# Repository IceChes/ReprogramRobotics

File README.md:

# ReprogramRobotics
This repository contains the raw firmware for my combat robots, as well as CAD and information about the ones that I've designed.

# Firmware Folder
Contains as-is firmware files. You should be able to work with Arduino directly in here. There are also compiled firmware files in here. If you want documentation for non-prototype firmware, that's also in here. All firmware, unless noted otherwise, is GPL3 licensed.

# Hardware Folder
Non-robot pieces of hardware, including Kicad workspaces, pieces of universal hardware (of which this ecosystem has few), and transmitter versions. All hardware, unless noted otherwise, is under the OHL-W license.

# Robot CAD Folder
Robot CAD and fab files, occasionally including build instructions and BOMs. All robots are of original design and licensed under OHL-W.

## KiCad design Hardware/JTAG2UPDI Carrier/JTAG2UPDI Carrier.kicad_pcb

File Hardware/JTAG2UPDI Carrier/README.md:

jtag2updi is no longer recommended as a protocol for programming UPDI chips. I just find it to be very easy to use.

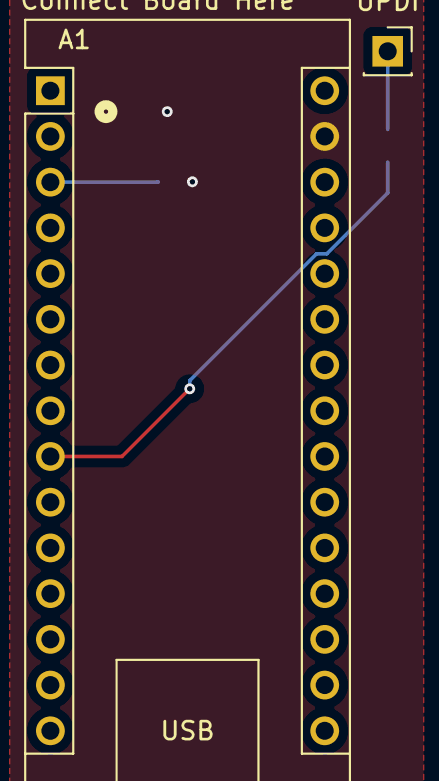
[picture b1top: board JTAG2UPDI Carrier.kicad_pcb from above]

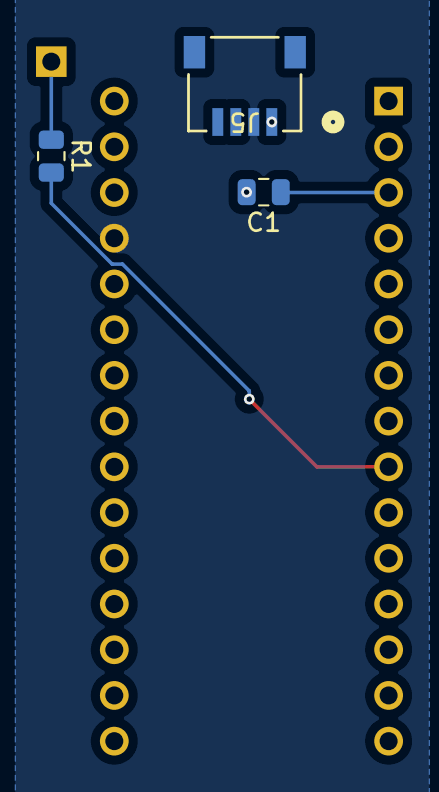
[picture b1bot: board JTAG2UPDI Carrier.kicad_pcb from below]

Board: 2 copper layers, 5 parts (3 on the bottom side), 5 nets.

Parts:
A1: Arduino_Nano_v3.x; Arduino_Nano
C1: C; C_0805_2012Metric
J5: PRT-14417; CONN_PRT-14417_SPK
R1: R; R_0805_2012Metric
UPDI: Conn_01x01_Socket; PinSocket_1x01_P2.54mm_Vertical

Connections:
+5V: A1.27 (+5V), J5.2
GND: A1.29 (GND), C1.2, J5.1
unnamed: A1.9 (D6), R1.2
unnamed: A1.3 (~RESET), C1.1
unnamed: R1.1, UPDI.1

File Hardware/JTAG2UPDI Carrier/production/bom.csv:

Designator,Footprint,Quantity,Value,LCSC Part #
A1,Arduino_Nano,1,Arduino_Nano_v3.x,
C1,0805,1,C,
J5,CONN_PRT-14417_SPK,1,PRT-14417,
R1,0805,1,R,
UPDI,PinSocket_1x01_P2.54mm_Vertical,1,Conn_01x01_Socket,

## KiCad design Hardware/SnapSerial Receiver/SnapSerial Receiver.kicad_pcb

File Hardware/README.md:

# Hardware
3D files and PCBs that aren't robots.

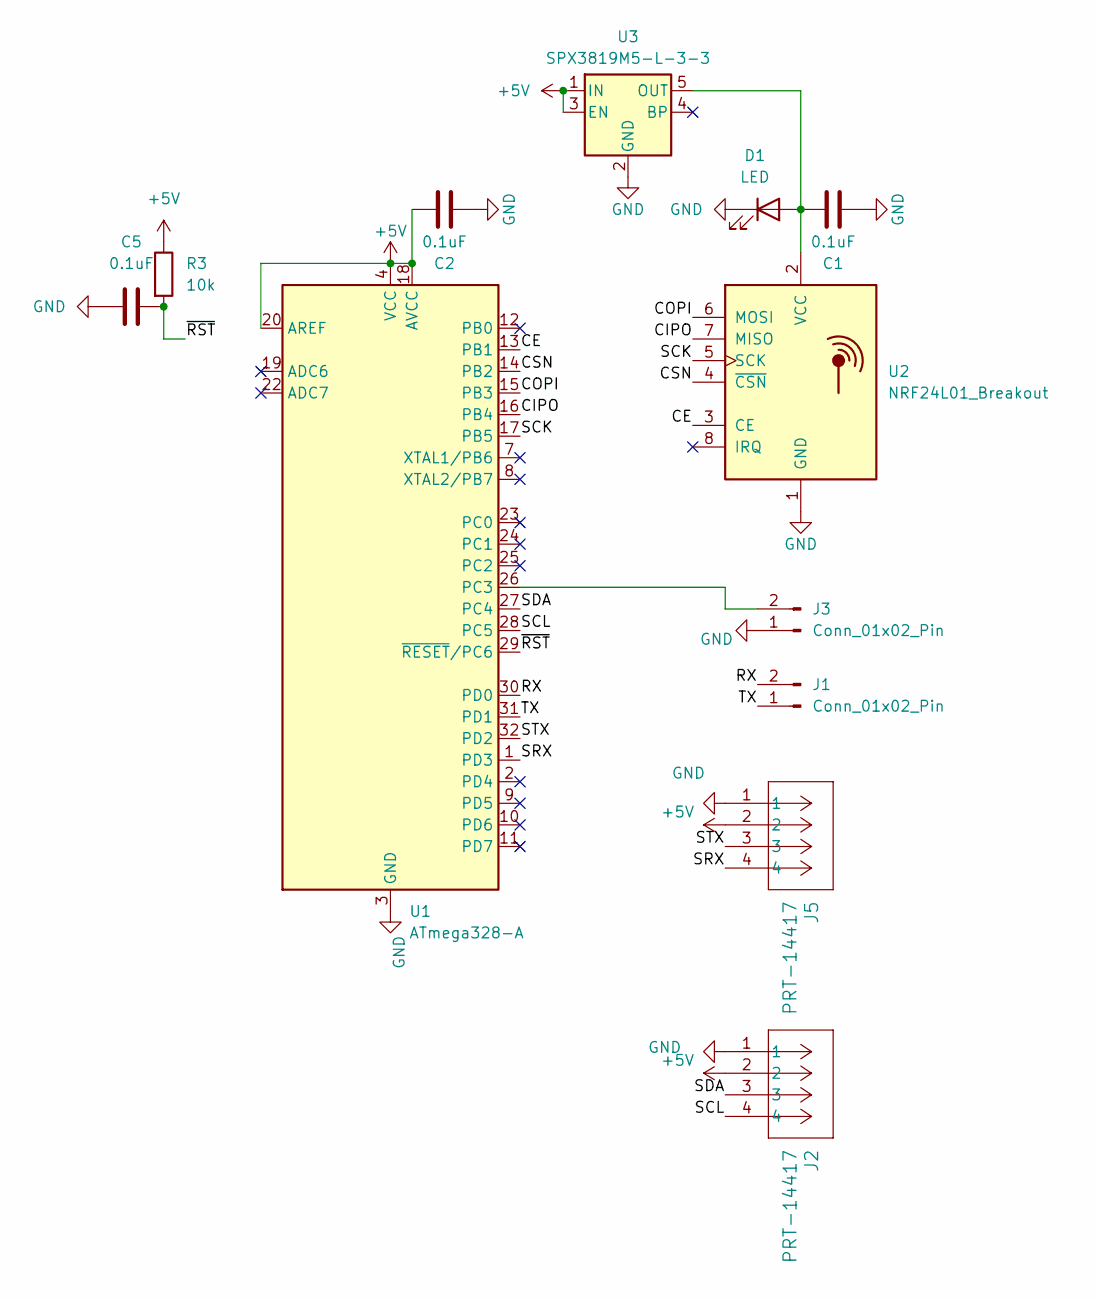
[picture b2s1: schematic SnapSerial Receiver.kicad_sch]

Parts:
C1, C2, C5: 0.1uF; C_0805_2012Metric
D1: LED; LED_0805_2012Metric
J1, J3: Conn_01x02_Pin; PinHeader_1x02_P2.54mm_Vertical
J2, J5: PRT-14417; CONN_PRT-14417_SPK
R3: 10k; R_0805_2012Metric
U1: ATmega328-A; TQFP-32_7x7mm_P0.8mm
U2: NRF24L01_Breakout; nRF24L01_Breakout
U3: SPX3819M5-L-3-3; SOT-23-5

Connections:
+5V: C2.2, J2.2, J5.2, R3.1, U1.4 (VCC), U1.6 (VCC), U1.18 (AVCC), U1.20 (AREF), U3.1 (IN), U3.3 (EN)
/CE: U1.13 (PB1), U2.3 (CE)
/CIPO: U1.16 (PB4), U2.7 (MISO)
/COPI: U1.15 (PB3), U2.6 (MOSI)
/CSN: U1.14 (PB2), U2.4 (~CSN)
/RX: J1.2, U1.30 (PD0)
/SCK: U1.17 (PB5), U2.5 (SCK)
/SCL: J2.4, U1.28 (PC5)
/SDA: J2.3, U1.27 (PC4)
/SRX: J5.4, U1.1 (PD3)
/STX: J5.3, U1.32 (PD2)
/TX: J1.1, U1.31 (PD1)
/~RST: C5.2, R3.2, U1.29 (~RESET/PC6)
GND: C1.1, C2.1, C5.1, D1.1 (K), J2.1, J3.1, J5.1, U1.3 (GND), U1.5 (GND), U1.21 (GND), U2.1 (GND), U3.2 (GND)
unnamed: C1.2, D1.2 (A), U2.2 (VCC), U3.5 (OUT)
unnamed: J3.2, U1.26 (PC3)

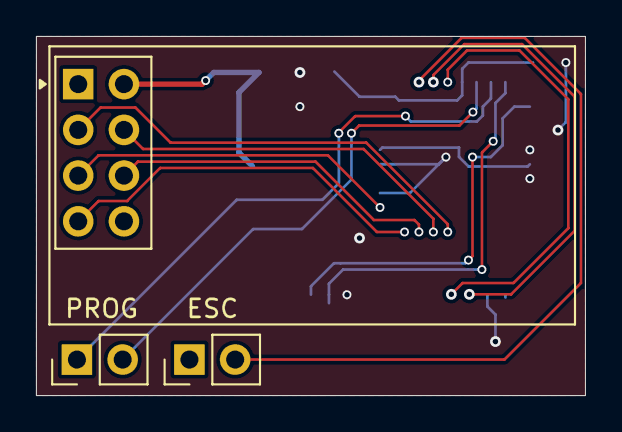
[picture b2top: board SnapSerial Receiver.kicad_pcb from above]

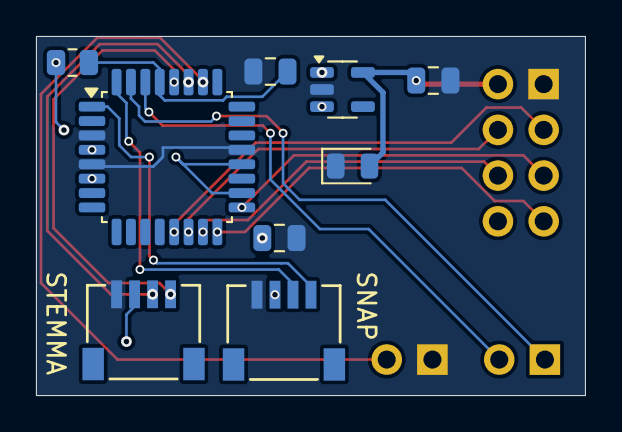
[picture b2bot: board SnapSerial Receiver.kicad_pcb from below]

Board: 2 copper layers, 30.5 x 20.0 mm, 12 parts (9 on the bottom side), 16 nets.

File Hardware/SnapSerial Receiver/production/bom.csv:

Designator,Footprint,Quantity,Value,LCSC Part #
"C1, C2, C5",0805,3,0.1uF,
D1,0805,1,LED,
"J1, J3",PinHeader_1x02_P2.54mm_Vertical,2,Conn_01x02_Pin,
"J2, J5",CONN_PRT-14417_SPK,2,PRT-14417,
R3,0805,1,10k,
U1,TQFP-32_7x7mm_P0.8mm,1,ATmega328-A,
U2,nRF24L01_Breakout,1,NRF24L01_Breakout,
U3,SOT-23-5,1,SPX3819M5-L-3-3,

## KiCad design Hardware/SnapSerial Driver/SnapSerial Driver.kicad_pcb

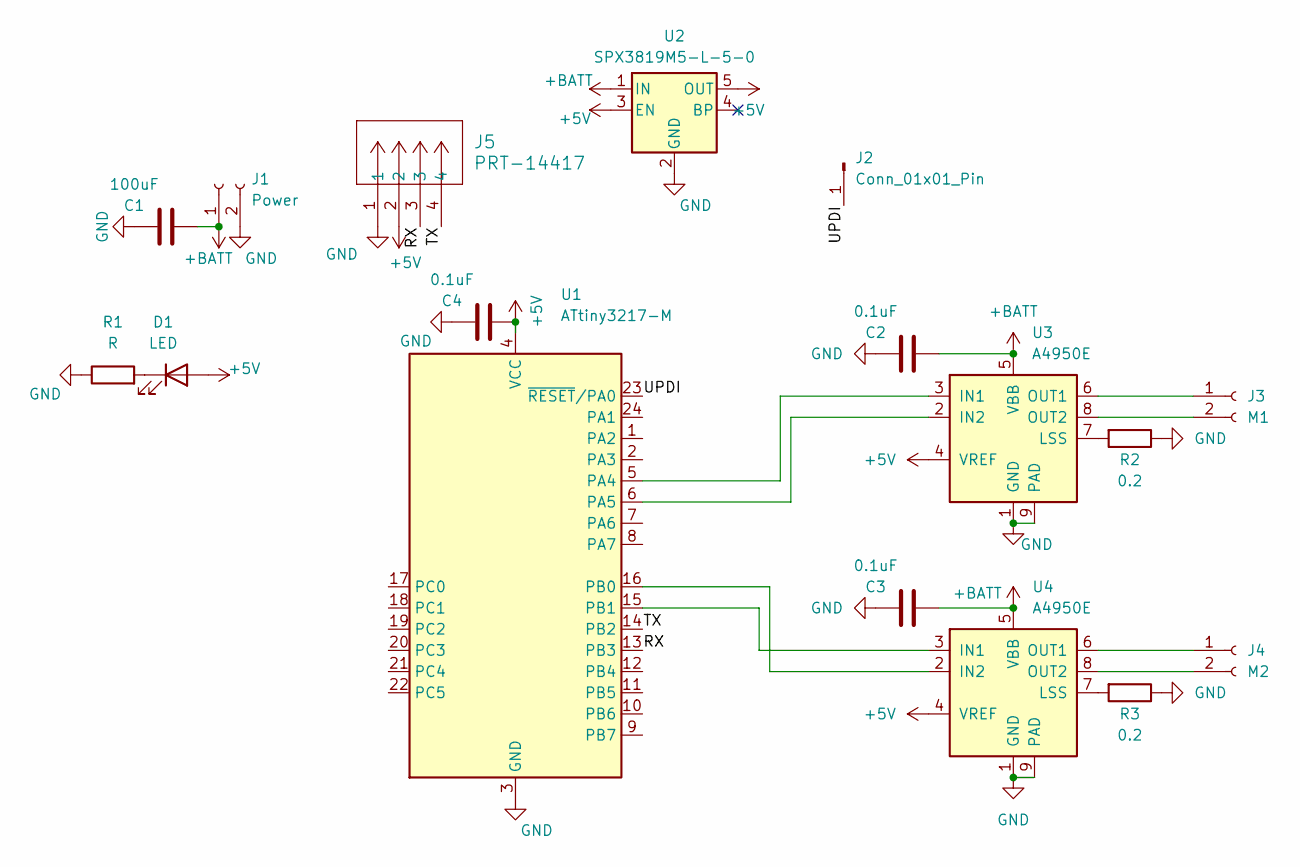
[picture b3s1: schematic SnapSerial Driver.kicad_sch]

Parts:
C1: 100uF; C_1206_3216Metric
C2, C3, C4: 0.1uF; C_0805_2012Metric
D1: LED; LED_0805_2012Metric
J1: Power; PinSocket_1x02_P2.54mm_Vertical
J2: Conn_01x01_Pin; PinHeader_1x01_P2.54mm_Vertical
J3: M1; PinSocket_1x02_P2.54mm_Vertical
J4: M2; PinSocket_1x02_P2.54mm_Vertical
J5: PRT-14417; CONN_PRT-14417_SPK
R1: R; R_0805_2012Metric
R2, R3: 0.2; R_0805_2012Metric
U1: ATtiny3217-M; QFN-24-1EP_4x4mm_P0.5mm_EP2.6x2.6mm
U2: SPX3819M5-L-5-0; SOT-23-5
U3, U4: A4950E; SOIC-8-1EP_3.9x4.9mm_P1.27mm_EP2.41x3.3mm

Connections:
+5V: C4.1, D1.2 (A), J5.2, U1.4 (VCC), U2.3 (EN), U2.5 (OUT), U3.4 (VREF), U4.4 (VREF)
+BATT: C1.1, C2.1, C3.1, J1.1, U2.1 (IN), U3.5 (VBB), U4.5 (VBB)
/RX: J5.3, U1.13 (PB3)
/TX: J5.4, U1.14 (PB2)
/UPDI: J2.1, U1.23 (~RESET/PA0)
GND: C1.2, C2.2, C3.2, C4.2, J1.2, J5.1, R1.1, R2.1, R3.1, U1.3 (GND), U1.25 (GND), U2.2 (GND), U3.1 (GND), U3.9 (PAD), U4.1 (GND), U4.9 (PAD)
unnamed: D1.1 (K), R1.2
unnamed: J3.1, U3.6 (OUT1)
unnamed: J3.2, U3.8 (OUT2)
unnamed: J4.1, U4.6 (OUT1)
unnamed: J4.2, U4.8 (OUT2)
unnamed: U1.5 (PA4), U3.3 (IN1)
unnamed: U1.6 (PA5), U3.2 (IN2)
unnamed: U1.16 (PB0), U4.2 (IN2)
unnamed: U1.15 (PB1), U4.3 (IN1)
unnamed: R2.2, U3.7 (LSS)
unnamed: R3.2, U4.7 (LSS)

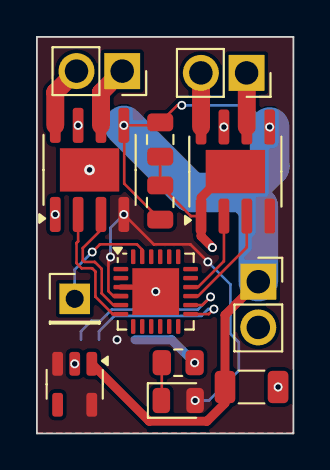
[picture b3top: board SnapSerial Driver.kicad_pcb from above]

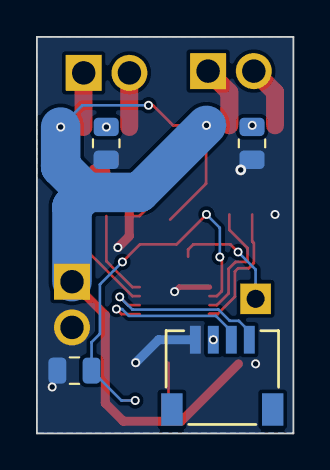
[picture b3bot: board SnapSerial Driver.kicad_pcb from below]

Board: 2 copper layers, 14.2 x 22.0 mm, 17 parts (4 on the bottom side), 17 nets.

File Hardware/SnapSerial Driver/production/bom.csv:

Designator,Footprint,Quantity,Value,LCSC Part #
C1,1206,1,100uF,
"C2, C3, C4",0805,3,0.1uF,
D1,0805,1,LED,
J1,PinSocket_1x02_P2.54mm_Vertical,1,Power,
J2,PinHeader_1x01_P2.54mm_Vertical,1,Conn_01x01_Pin,
J3,PinSocket_1x02_P2.54mm_Vertical,1,M1,
J4,PinSocket_1x02_P2.54mm_Vertical,1,M2,
J5,CONN_PRT-14417_SPK,1,PRT-14417,
R1,0805,1,R,
"R2, R3",0805,2,0.2,
U1,QFN-24-1EP_4x4mm_P0.5mm_EP2.6x2.6mm,1,ATtiny3217-M,
U2,SOT-23-5,1,SPX3819M5-L-5-0,
"U3, U4",SOIC-8-1EP_3.9x4.9mm_P1.27mm_EP2.41x3.3mm,2,A4950E,

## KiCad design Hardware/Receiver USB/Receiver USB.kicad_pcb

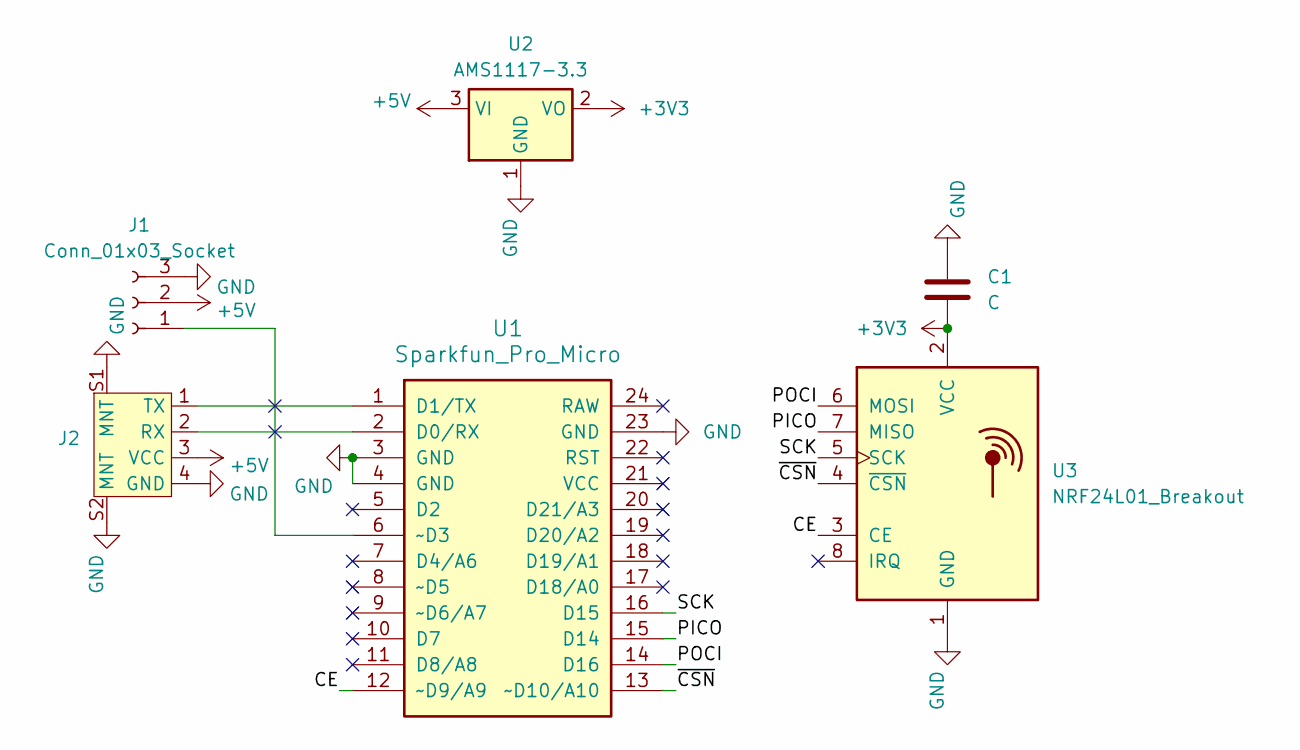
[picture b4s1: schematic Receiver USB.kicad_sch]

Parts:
C1: C; C_0805_2012Metric
J1: Conn_01x03_Socket; PinHeader_1x03_P2.54mm_Vertical
J2: SPARKFUN_PRT-14417
U1: Sparkfun_Pro_Micro
U2: AMS1117-3.3; SOT-223-3_TabPin2
U3: NRF24L01_Breakout; nRF24L01_Breakout

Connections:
+3V3: C1.2, U2.2 (VO), U3.2 (VCC)
+5V: J1.2, J2.3 (VCC), U2.3 (VI)
/CE: U1.12 (~D9/A9), U3.3 (CE)
/PICO: U1.15 (D14), U3.7 (MISO)
/POCI: U1.14 (D16), U3.6 (MOSI)
/SCK: U1.16 (D15), U3.5 (SCK)
/~CSN: U1.13 (~D10/A10), U3.4 (~CSN)
GND: C1.1, J1.3, J2.4 (GND), J2.S1 (MNT), J2.S2 (MNT), U1.3 (GND), U1.4 (GND), U1.23 (GND), U2.1 (GND), U3.1 (GND)
unnamed: J1.1, U1.6 (~D3)
unnamed: J2.2 (RX), U1.2 (D0/RX)
unnamed: J2.1 (TX), U1.1 (D1/TX)

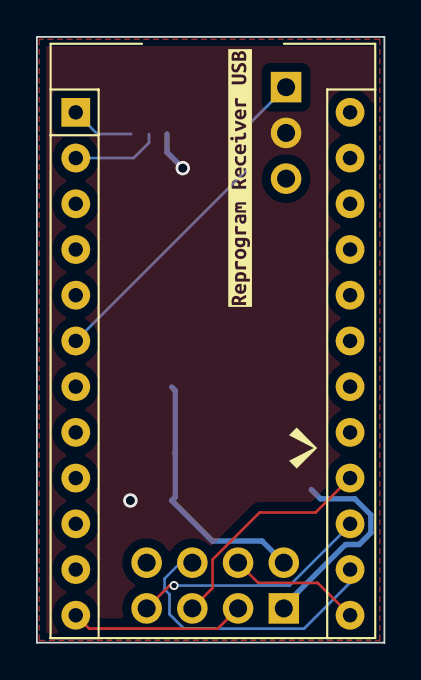
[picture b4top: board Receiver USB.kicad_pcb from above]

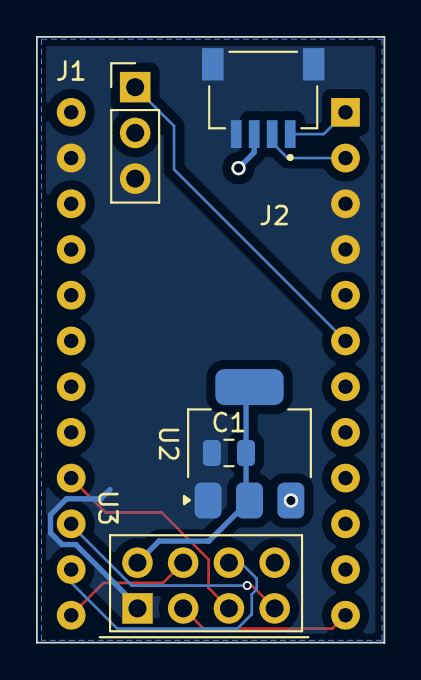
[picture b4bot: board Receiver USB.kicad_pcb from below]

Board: 2 copper layers, 19.3 x 33.7 mm, 7 parts (5 on the bottom side), 11 nets.

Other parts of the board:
kibuzzard-67BFB299: G***; kibuzzard-67BFB299

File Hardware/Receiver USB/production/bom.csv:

Designator,Footprint,Quantity,Value,LCSC Part #
C1,0805,1,C,
J1,PinHeader_1x03_P2.54mm_Vertical,1,Conn_01x03_Socket,
J2,SPARKFUN_PRT-14417,1,~,
U1,Sparkfun_Pro_Micro,1,Sparkfun_Pro_Micro,
U2,SOT-223-3_TabPin2,1,AMS1117-3.3,
U3,nRF24L01_Breakout,1,NRF24L01_Breakout,

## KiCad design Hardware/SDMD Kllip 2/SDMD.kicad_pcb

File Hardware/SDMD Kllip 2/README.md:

# Software Defined Motor Driver
An actually good brushed DESC that you can reprogram in the Arduino IDE. SDMD will shut down if the outputs are short circuited. This version of SDMD is fully working and can be sent out for fab and used with the sdmd.ino.hex machine code in the FW folder.

# SDMD Details
- atmega328 (not P) MCU
- A4950E motor driver
- AMS1117-5 BEC
- 100uF input capacitor

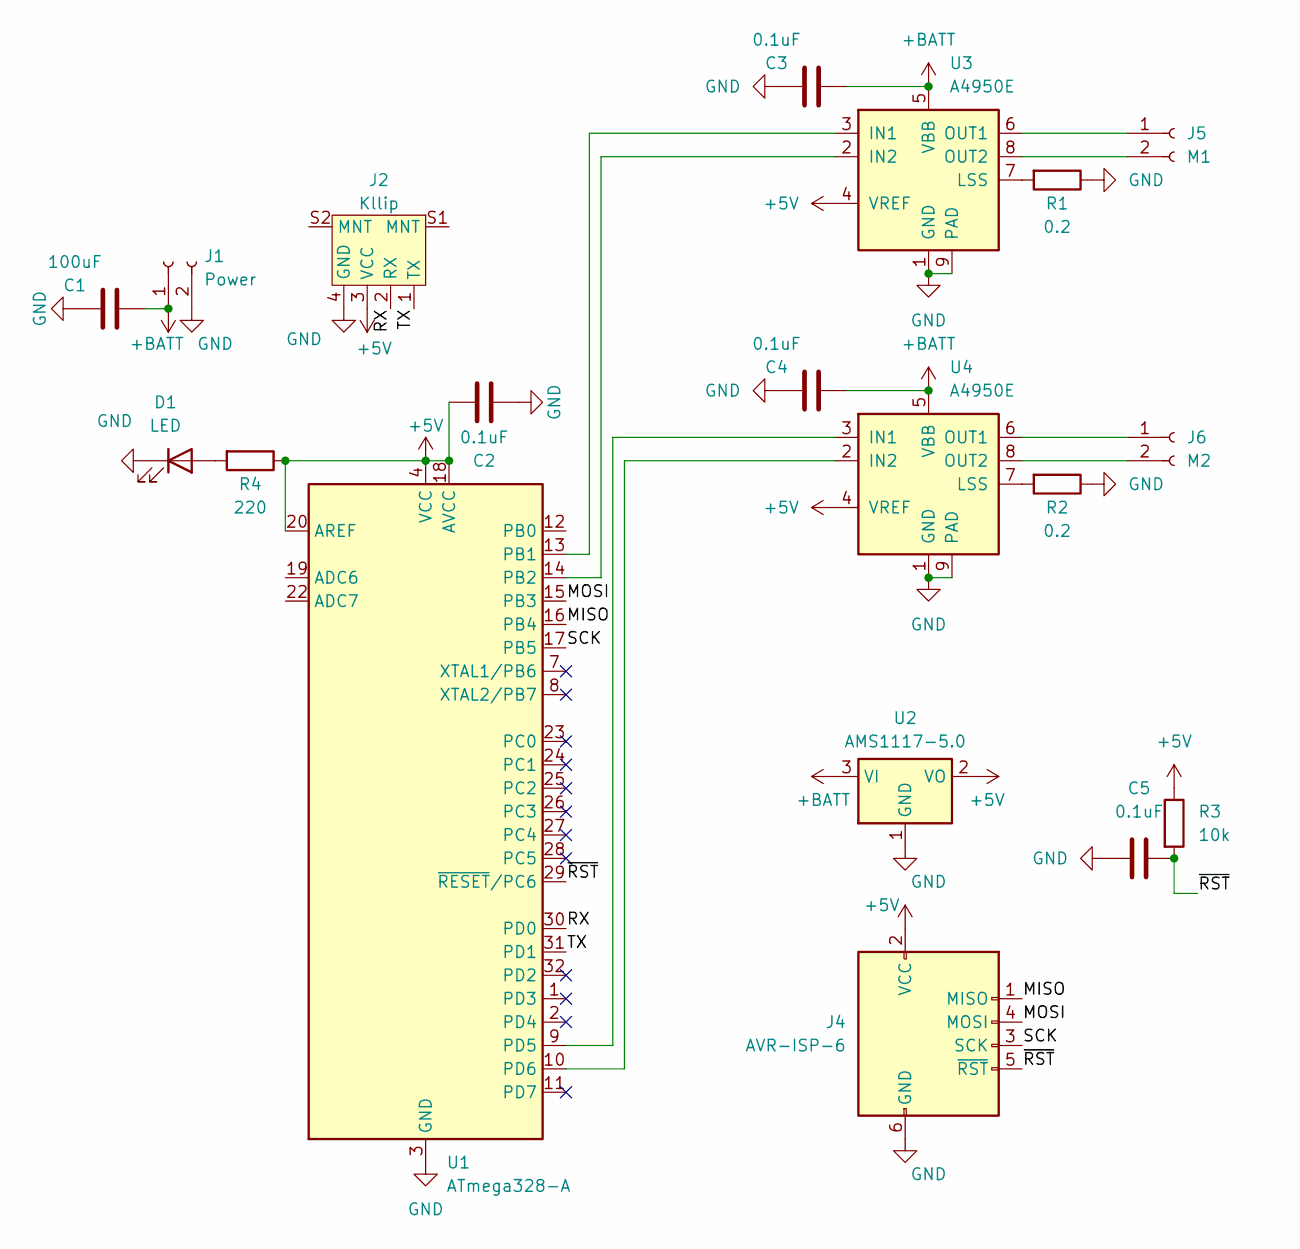
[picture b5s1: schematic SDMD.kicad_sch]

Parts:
C1: 100uF; C_1206_3216Metric
C2, C3, C4, C5: 0.1uF; C_0805_2012Metric
D1: LED; LED_0805_2012Metric
J1: Power; PinSocket_1x02_P2.54mm_Vertical
J2: Kllip; SPARKFUN_PRT-14417
J4: AVR-ISP-6; PinSocket_2x03_P2.54mm_Vertical
J5: M1; PinSocket_1x02_P2.54mm_Vertical
J6: M2; PinSocket_1x02_P2.54mm_Vertical
R1, R2: 0.2; R_0805_2012Metric
R3: 10k; R_0805_2012Metric
R4: 220; R_0805_2012Metric
U1: ATmega328-A; TQFP-32_7x7mm_P0.8mm
U2: AMS1117-5.0; SOT-223-3_TabPin2
U3, U4: A4950E; SOIC-8-1EP_3.9x4.9mm_P1.27mm_EP2.41x3.3mm

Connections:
+5V: C2.2, J2.3 (VCC), J4.2 (VCC), R3.1, R4.1, U1.4 (VCC), U1.6 (VCC), U1.18 (AVCC), U1.20 (AREF), U2.2 (VO), U3.4 (VREF), U4.4 (VREF)
+BATT: C1.1, C3.1, C4.1, J1.1, U2.3 (VI), U3.5 (VBB), U4.5 (VBB)
/MISO: J4.1 (MISO), U1.16 (PB4)
/MOSI: J4.4 (MOSI), U1.15 (PB3)
/RX: J2.2 (RX), U1.30 (PD0)
/SCK: J4.3 (SCK), U1.17 (PB5)
/TX: J2.1 (TX), U1.31 (PD1)
/~RST: C5.2, J4.5 (~RST), R3.2, U1.29 (~RESET/PC6)
GND: C1.2, C2.1, C3.2, C4.2, C5.1, D1.1 (K), J1.2, J2.4 (GND), J4.6 (GND), R1.1, R2.1, U1.3 (GND), U1.5 (GND), U1.21 (GND), U2.1 (GND), U3.1 (GND), U3.9 (PAD), U4.1 (GND), U4.9 (PAD)
unnamed: D1.2 (A), R4.2
unnamed: J5.1, U3.6 (OUT1)
unnamed: J5.2, U3.8 (OUT2)
unnamed: J6.1, U4.6 (OUT1)
unnamed: J6.2, U4.8 (OUT2)
unnamed: U1.13 (PB1), U3.3 (IN1)
unnamed: U1.14 (PB2), U3.2 (IN2)
unnamed: U1.9 (PD5), U4.3 (IN1)
unnamed: U1.10 (PD6), U4.2 (IN2)
unnamed: R1.2, U3.7 (LSS)
unnamed: R2.2, U4.7 (LSS)

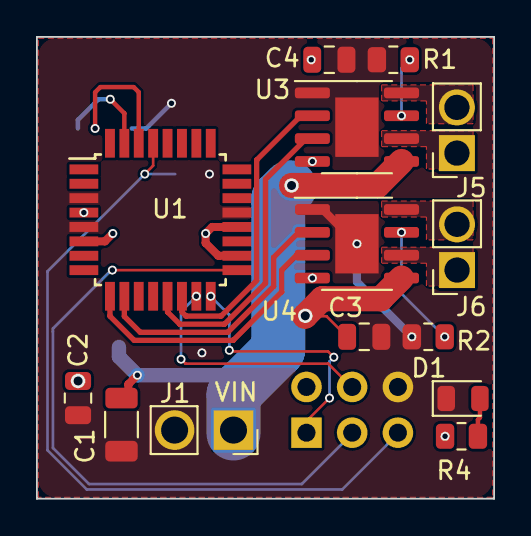
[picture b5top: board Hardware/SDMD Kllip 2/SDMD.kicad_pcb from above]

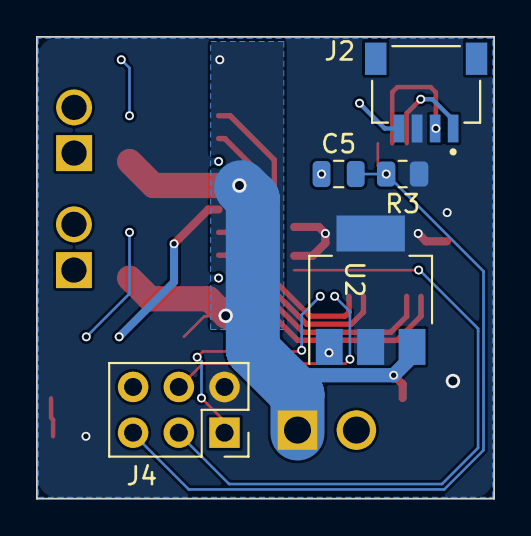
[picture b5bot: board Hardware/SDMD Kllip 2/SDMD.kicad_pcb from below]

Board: 2 copper layers, 25.4 x 25.7 mm, 20 parts (5 on the bottom side), 20 nets.

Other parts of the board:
kibuzzard-6781F98D: G***; kibuzzard-6781F98D

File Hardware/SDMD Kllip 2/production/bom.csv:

Designator,Footprint,Quantity,Value,LCSC Part #
C1,1206,1,100uF,
"C2, C3, C4, C5",0805,4,0.1uF,
D1,0805,1,LED,
J1,PinSocket_1x02_P2.54mm_Vertical,1,Power,
J2,SPARKFUN_PRT-14417,1,Kllip,
J4,PinSocket_2x03_P2.54mm_Vertical,1,AVR-ISP-6,
J5,PinSocket_1x02_P2.54mm_Vertical,1,M1,
J6,PinSocket_1x02_P2.54mm_Vertical,1,M2,
"R1, R2",0805,2,0.2,
R3,0805,1,10k,
R4,0805,1,220,
U1,TQFP-32_7x7mm_P0.8mm,1,ATmega328-A,
U2,SOT-223-3_TabPin2,1,AMS1117-5.0,
"U3, U4",SOIC-8-1EP_3.9x4.9mm_P1.27mm_EP2.41x3.3mm,2,A4950E,

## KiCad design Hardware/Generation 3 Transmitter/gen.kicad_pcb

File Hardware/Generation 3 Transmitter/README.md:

# Parts
3D part files for the gen 3 transmitter.

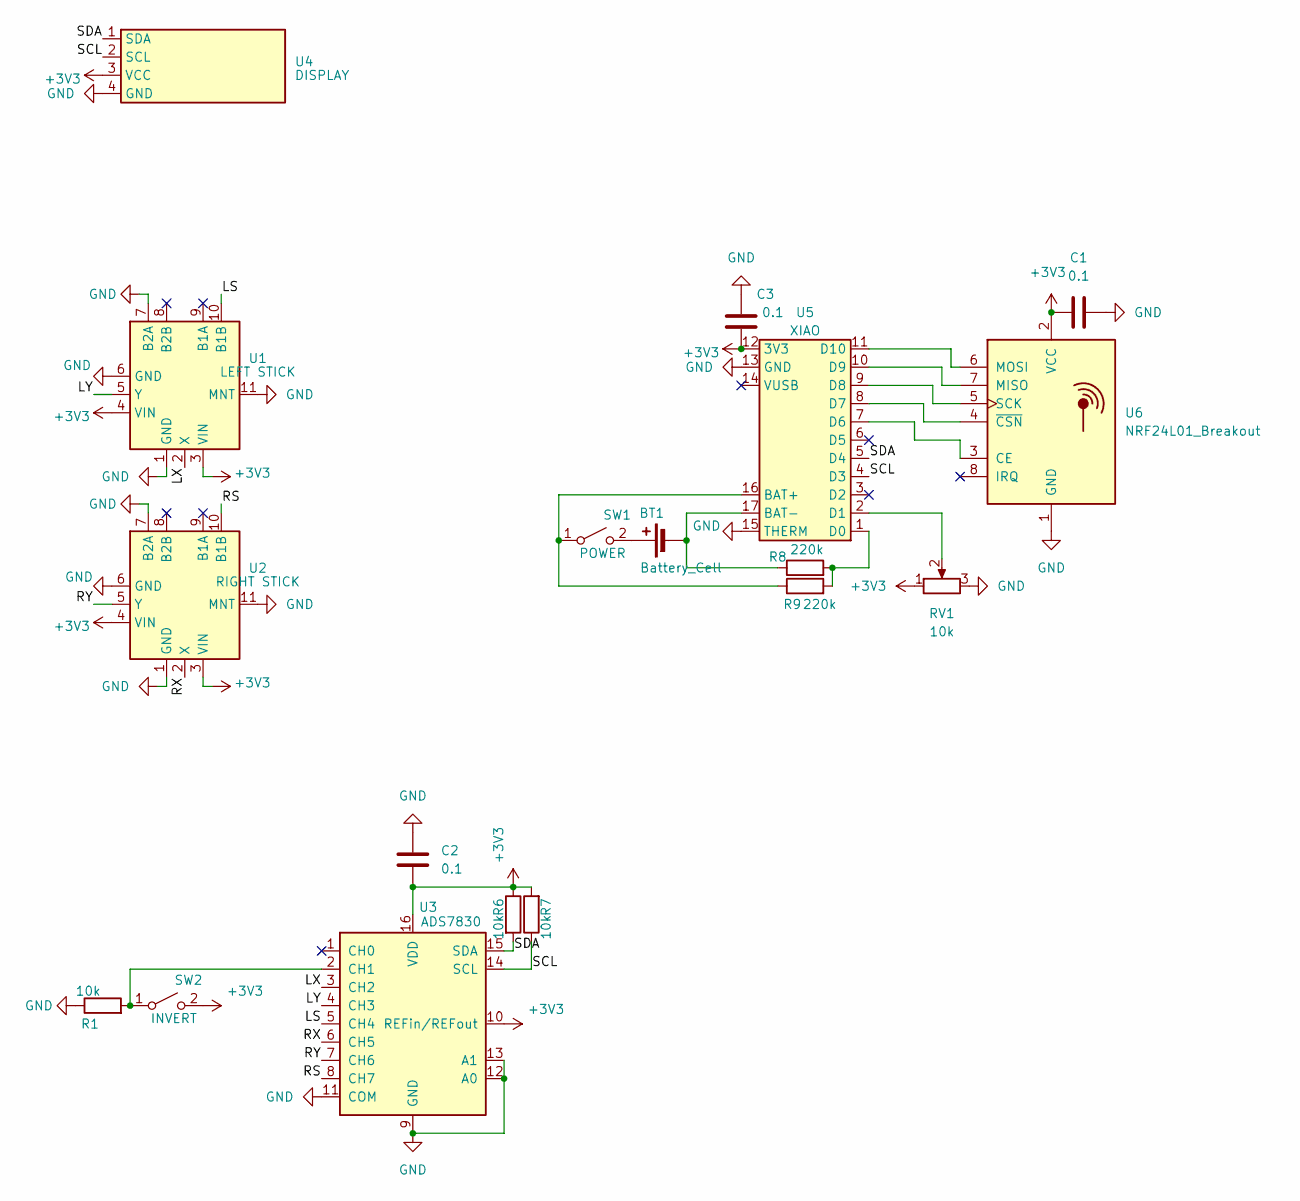
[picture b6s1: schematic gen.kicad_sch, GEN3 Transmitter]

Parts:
BT1: Battery_Cell; PinHeader_1x02_P2.54mm_Vertical
C1, C2, C3: 0.1; C_0805_2012Metric
R1, R6, R7: 10k; R_0805_2012Metric
R8, R9: 220k; R_0805_2012Metric
RV1: 10k; PinSocket_1x03_P2.54mm_Vertical
SW1: POWER; PinSocket_1x02_P2.54mm_Vertical
SW2: INVERT; PinSocket_1x02_P2.54mm_Vertical
U1: LEFT STICK; JOYSTICK
U2: RIGHT STICK; JOYSTICK
U3: ADS7830; TSSOP-16_4.4x5mm_P0.65mm
U4: DISPLAY; PinSocket_1x04_P2.54mm_Vertical
U5: XIAO; MCU_Seeed_ESP32C3
U6: NRF24L01_Breakout; nRF24L01_Breakout

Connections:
+3V3: C1.1, C2.1, C3.1, R6.1, R7.2, RV1.1, SW2.2 (B), U1.3 (VIN), U1.4 (VIN), U2.3 (VIN), U2.4 (VIN), U3.10 (REFin/REFout), U3.16 (VDD), U4.3 (VCC), U5.12 (3V3), U6.2 (VCC)
/LS: U1.10 (B1B), U3.5 (CH4)
/LX: U1.2 (X), U3.3 (CH2)
/LY: U1.5 (Y), U3.4 (CH3)
/RS: U2.10 (B1B), U3.8 (CH7)
/RX: U2.2 (X), U3.6 (CH5)
/RY: U2.5 (Y), U3.7 (CH6)
/SCL: R7.1, U3.14 (SCL), U4.2 (SCL), U5.4 (D3)
/SDA: R6.2, U3.15 (SDA), U4.1 (SDA), U5.5 (D4)
GND: C1.2, C2.2, C3.2, R1.1, RV1.3, U1.1 (GND), U1.6 (GND), U1.7 (B2A), U1.11 (MNT), U2.1 (GND), U2.6 (GND), U2.7 (B2A), U2.11 (MNT), U3.9 (GND), U3.11 (COM), U3.12 (A0), U3.13 (A1), U4.4 (GND), U5.13 (GND), U5.15 (THERM), U6.1 (GND)
unnamed: BT1.1 (+), SW1.2 (B)
unnamed: BT1.2 (-), R8.1, U5.17 (BAT-)
unnamed: R9.1, SW1.1 (A), U5.16 (BAT+)
unnamed: R1.2, SW2.1 (A), U3.2 (CH1)
unnamed: R8.2, R9.2, U5.1 (D0)
unnamed: RV1.2, U5.2 (D1)
unnamed: U5.7 (D6), U6.3 (CE)
unnamed: U5.8 (D7), U6.4 (~CSN)
unnamed: U5.9 (D8), U6.5 (SCK)
unnamed: U5.10 (D9), U6.7 (MISO)
unnamed: U5.11 (D10), U6.6 (MOSI)

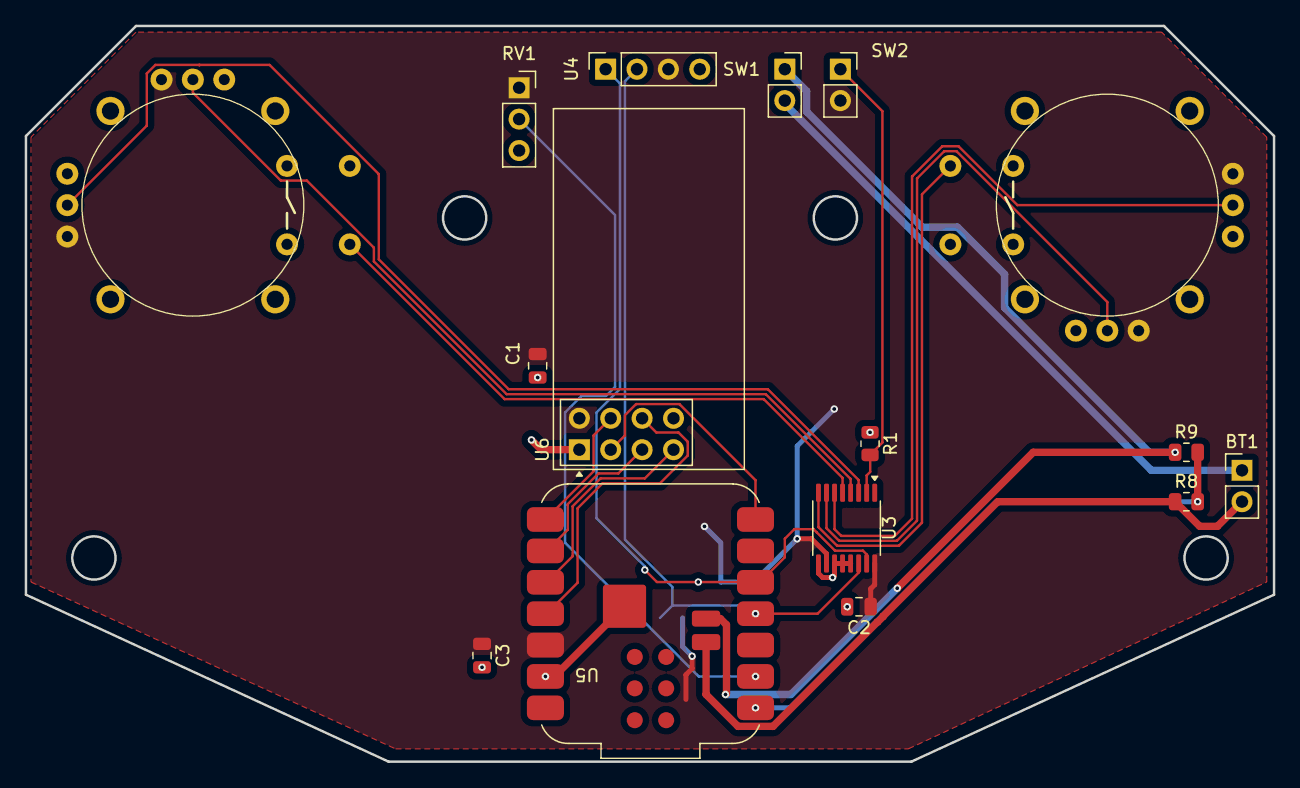
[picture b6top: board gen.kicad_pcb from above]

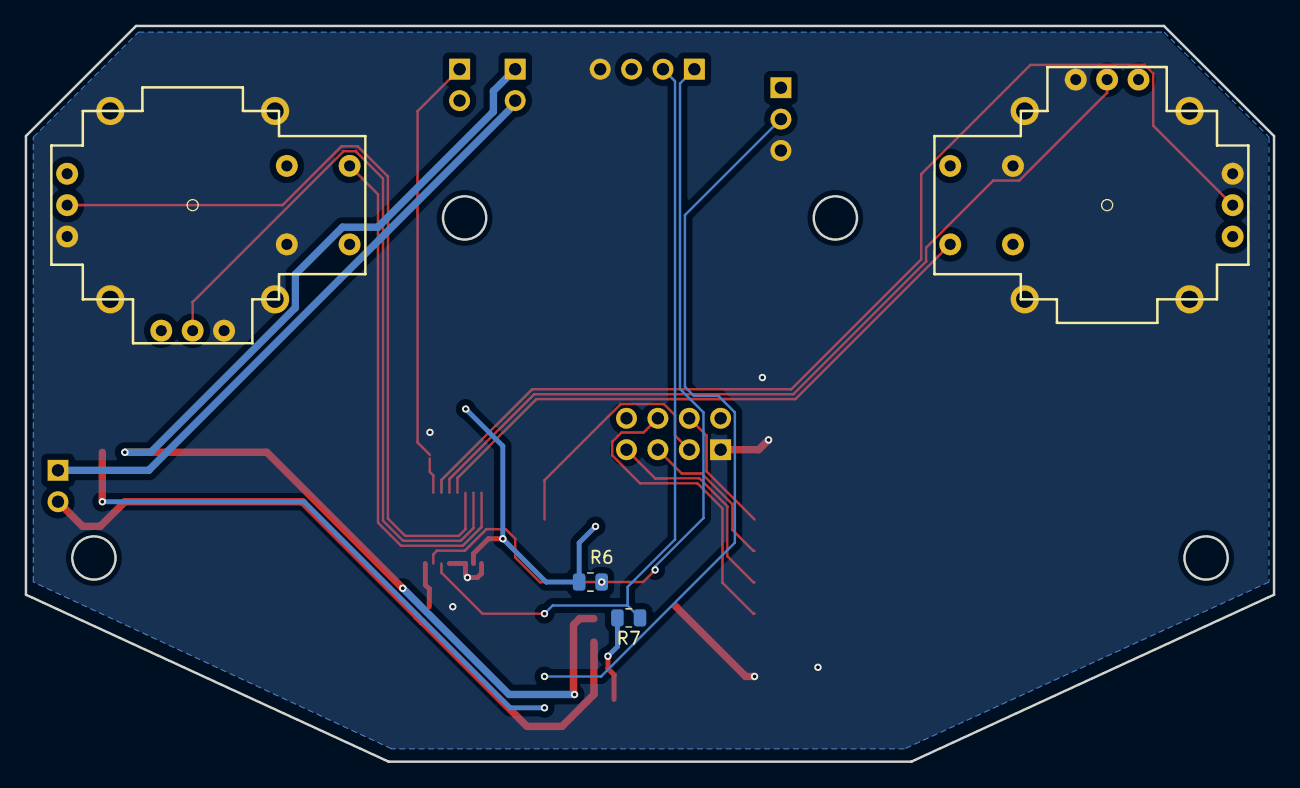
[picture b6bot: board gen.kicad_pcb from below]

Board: 2 copper layers, 101.0 x 59.5 mm, 18 parts (2 on the bottom side), 21 nets.

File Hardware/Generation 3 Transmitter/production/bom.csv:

Designator,Footprint,Quantity,Value,LCSC Part #
BT1,PinHeader_1x02_P2.54mm_Vertical,1,Battery_Cell,
"C1, C2, C3",0805,3,0.1,
"R1, R6, R7",0805,3,10k,
"R8, R9",0805,2,220k,
RV1,PinSocket_1x03_P2.54mm_Vertical,1,10k,
SW1,PinSocket_1x02_P2.54mm_Vertical,1,POWER,
SW2,PinSocket_1x02_P2.54mm_Vertical,1,INVERT,
U1,JOYSTICK,1,LEFT STICK,
U2,JOYSTICK,1,RIGHT STICK,
U3,TSSOP-16_4.4x5mm_P0.65mm,1,ADS7830,
U4,PinSocket_1x04_P2.54mm_Vertical,1,DISPLAY,
U5,MCU_Seeed_ESP32C3,1,XIAO,
U6,nRF24L01_Breakout,1,NRF24L01_Breakout,

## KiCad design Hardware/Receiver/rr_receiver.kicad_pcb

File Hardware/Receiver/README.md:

# RR Receiver
Prototype receiver to replace my old RF nanos.

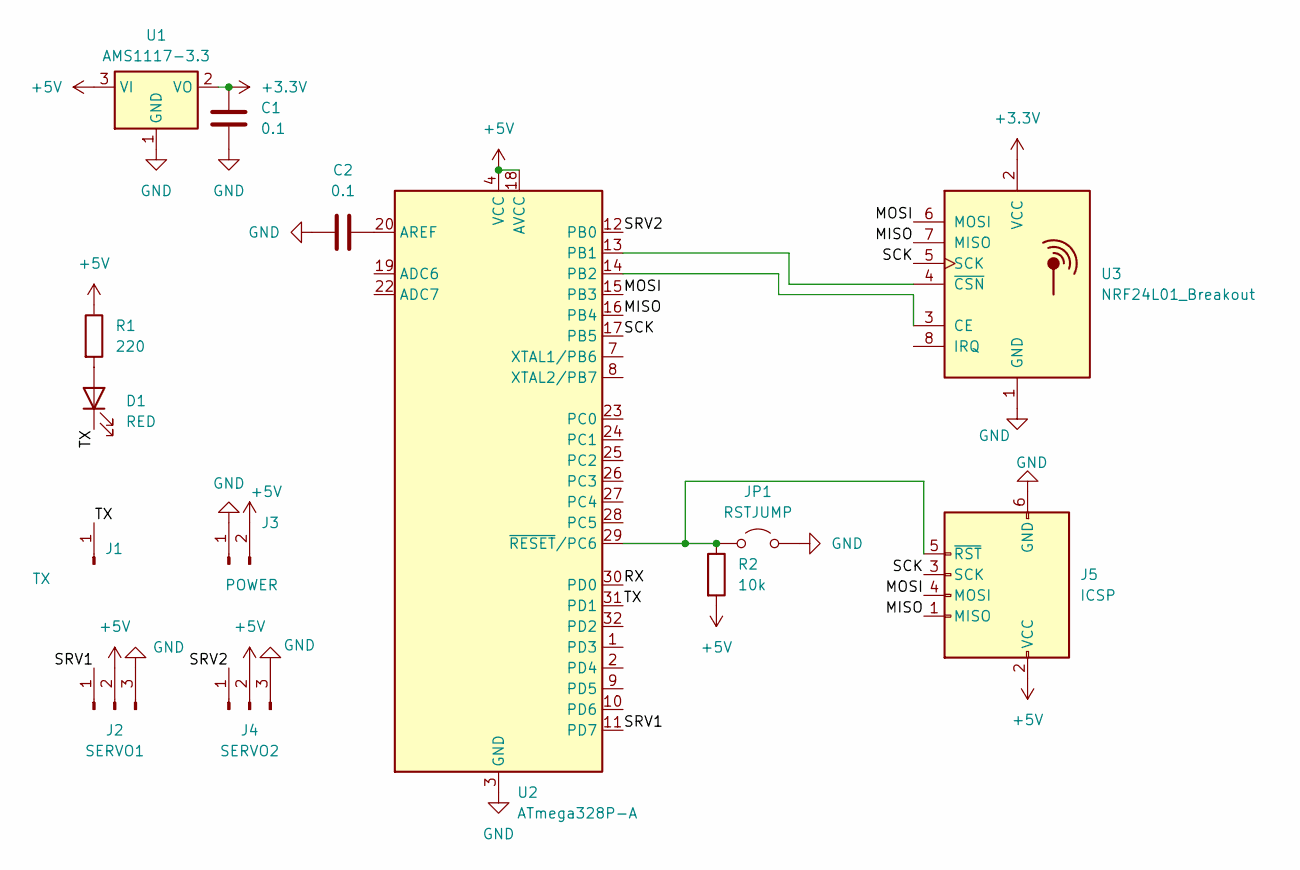
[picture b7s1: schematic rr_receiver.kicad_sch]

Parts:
C1, C2: 0.1; C_0805_2012Metric; LCSC C126469
D1: RED; LED_0805_2012Metric
J1: TX; PinSocket_1x01_P2.54mm_Vertical
J2: SERVO1; PinSocket_1x03_P2.54mm_Vertical
J3: POWER; PinSocket_1x02_P2.54mm_Vertical
J4: SERVO2; PinSocket_1x03_P2.54mm_Vertical
J5: ICSP; PinSocket_2x03_P2.54mm_Vertical
JP1: RSTJUMP; SolderJumper-2_P1.3mm_Open_Pad1.0x1.5mm
R1: 220; R_0805_2012Metric; LCSC C17557
R2: 10k; R_0805_2012Metric; LCSC C176201
U1: AMS1117-3.3; SOT-223-3_TabPin2; LCSC C6186
U2: ATmega328P-A; TQFP-32_7x7mm_P0.8mm; LCSC C618731
U3: NRF24L01_Breakout; nRF24L01_Breakout

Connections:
+3.3V: C1.1, U1.2 (VO), U3.2 (VCC)
+5V: J2.2, J3.2, J4.2, J5.2 (VCC), R1.1, R2.2, U1.3 (VI), U2.4 (VCC), U2.6 (VCC), U2.18 (AVCC)
/MISO: J5.1 (MISO), U2.16 (PB4), U3.7 (MISO)
/MOSI: J5.4 (MOSI), U2.15 (PB3), U3.6 (MOSI)
/RX: U2.30 (PD0)
/SCK: J5.3 (SCK), U2.17 (PB5), U3.5 (SCK)
/SRV1: J2.1, U2.11 (PD7)
/SRV2: J4.1, U2.12 (PB0)
/TX: D1.1 (K), J1.1, U2.31 (PD1)
GND: C1.2, C2.2, J2.3, J3.1, J4.3, J5.6 (GND), JP1.2 (B), U1.1 (GND), U2.3 (GND), U2.5 (GND), U2.21 (GND), U3.1 (GND)
unnamed: D1.2 (A), R1.2
unnamed: J5.5 (~RST), JP1.1 (A), R2.1, U2.29 (~RESET/PC6)
unnamed: C2.1, U2.20 (AREF)
unnamed: U2.13 (PB1), U3.4 (~CSN)
unnamed: U2.14 (PB2), U3.3 (CE)

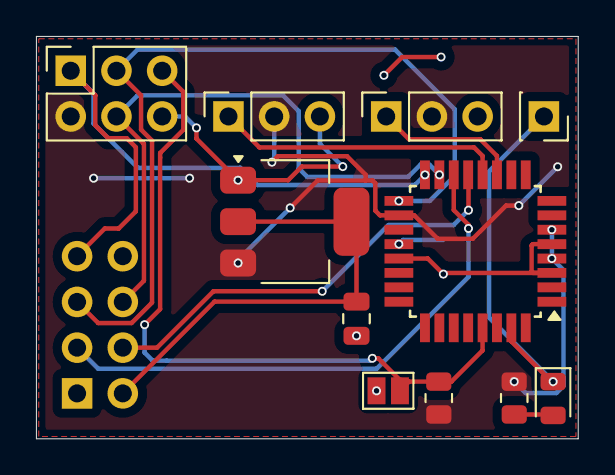
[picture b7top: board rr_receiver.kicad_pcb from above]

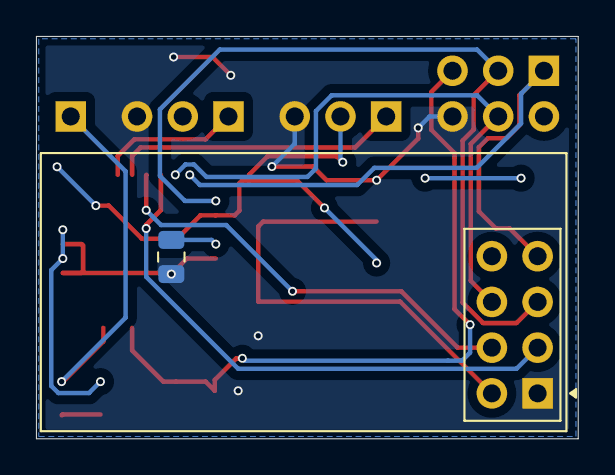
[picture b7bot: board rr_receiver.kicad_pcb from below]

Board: 2 copper layers, 30.1 x 22.4 mm, 13 parts (2 on the bottom side), 14 nets.

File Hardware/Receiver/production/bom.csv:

Designator,Footprint,Quantity,Value,LCSC Part #
"C1, C2",0805,2,0.1,C126469
D1,0805,1,RED,
J1,PinSocket_1x01_P2.54mm_Vertical,1,TX,
J2,PinSocket_1x03_P2.54mm_Vertical,1,SERVO1,
J4,PinSocket_1x03_P2.54mm_Vertical,1,SERVO2,
J5,PinSocket_2x03_P2.54mm_Vertical,1,ICSP,
JP1,SolderJumper-2_P1.3mm_Open_Pad1.0x1.5mm,1,RSTJUMP,
R1,0805,1,220,C17557
R2,0805,1,10k,C176201
U1,SOT-223-3_TabPin2,1,AMS1117-3.3,C6186
U2,TQFP-32_7x7mm_P0.8mm,1,ATmega328P-A,C618731
U3,nRF24L01_Breakout,1,NRF24L01_Breakout,
